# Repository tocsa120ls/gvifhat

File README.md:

gvifhat - a RasPi hat that uses the DVI output to create a GVIF stream that can be fed into an Opel Ampera/Chevy Volt's central display
---------------------------------------------------------------------------------------------------------------------------------------

### It also has an AR1100 HID to capture the touches from the display and feed it back to the RasPi. (and an RTC)

Proof-of-Concept video: [YouTube](https://youtube.com/shorts/U-wecjOfMDg?feature=share)

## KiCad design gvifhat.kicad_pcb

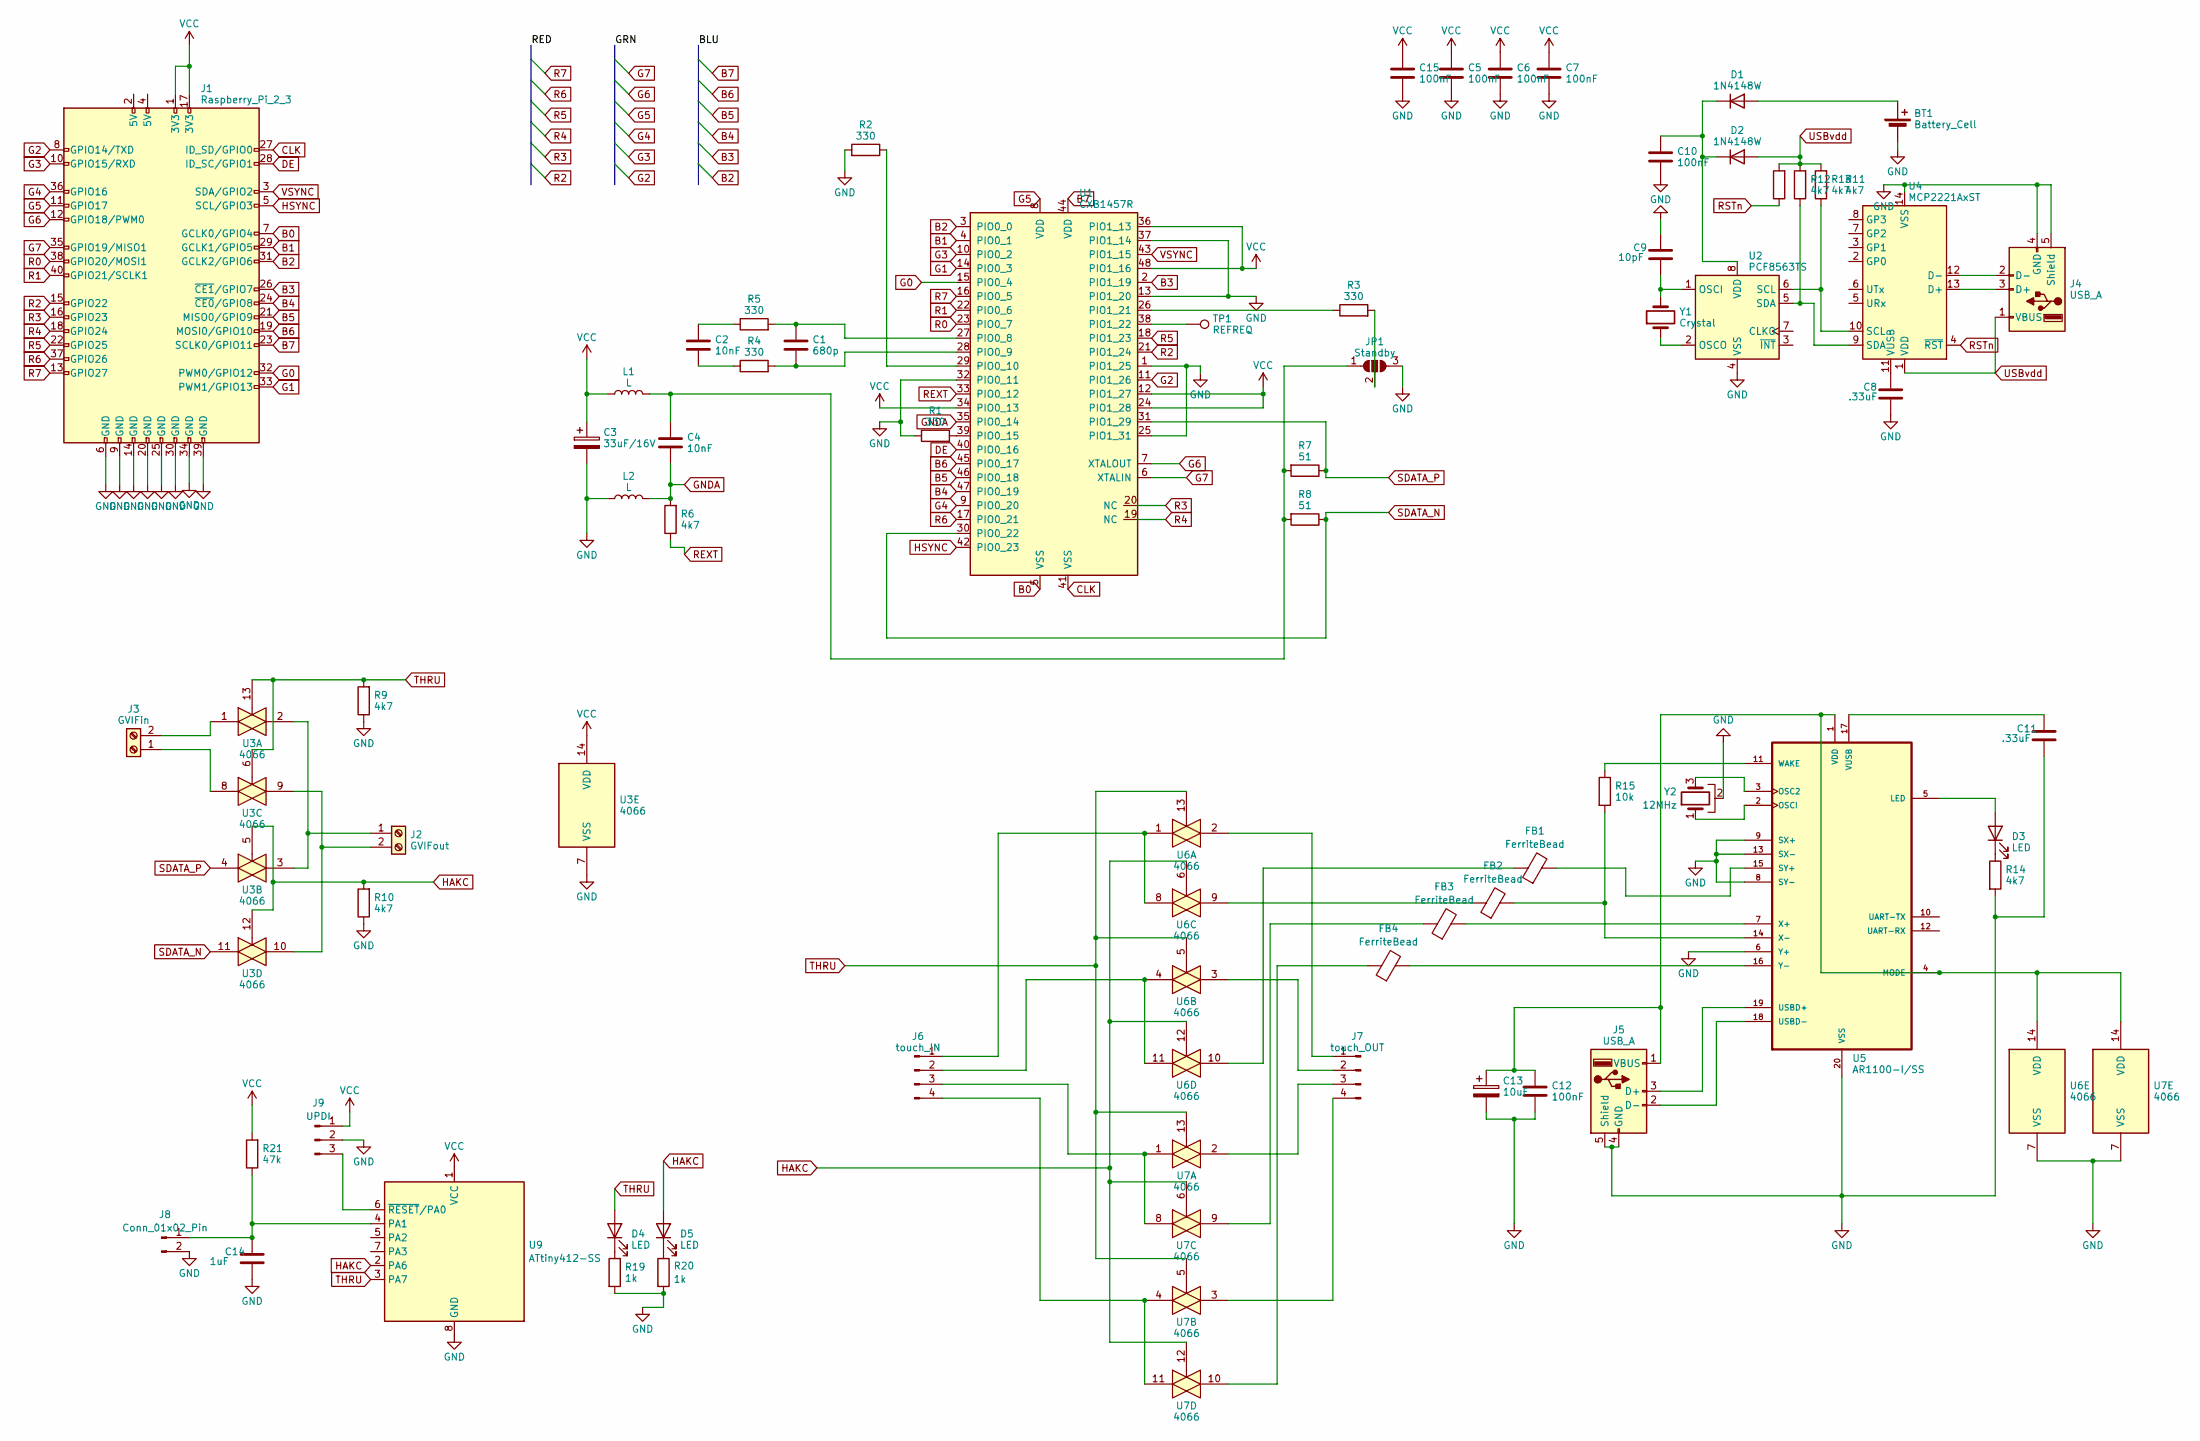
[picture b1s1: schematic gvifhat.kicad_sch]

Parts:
BT1: Battery_Cell; MPD_BC501SM-TR
C1: 680p; C_0603_1608Metric_Pad1.08x0.95mm_HandSolder
C2, C4: 10nF; C_0603_1608Metric_Pad1.08x0.95mm_HandSolder
C3: 33uF/16V; CP_EIA-6032-15_Kemet-U
C5, C6, C7, C10, C12, C15: 100nF; C_0603_1608Metric_Pad1.08x0.95mm_HandSolder
C8, C11: .33uF; C_0603_1608Metric_Pad1.08x0.95mm_HandSolder
C9: 10pF; C_0603_1608Metric_Pad1.08x0.95mm_HandSolder
C13: 10uF; CP_EIA-6032-15_Kemet-U
C14: 1uF; C_0603_1608Metric_Pad1.08x0.95mm_HandSolder
D1, D2: 1N4148W; D_SOD-123
D3, D4, D5: LED; LED_0603_1608Metric_Pad1.05x0.95mm_HandSolder
FB1, FB2, FB3, FB4: FerriteBead; R_0603_1608Metric
J1: Raspberry_Pi_2_3; MODULE_RASPBERRY_PI_4B_4GB
J2: GVIFout; TerminalBlock_Altech_AK300-2_P5.00mm
J3: GVIFin; TerminalBlock_Altech_AK300-2_P5.00mm
J4, J5: USB_A; USB_A_Molex_105057_Vertical
J6: touch_IN; FPC-SMD_3P-P1.00_AFA10-S03ECC-00
J7: touch_OUT; FPC-SMD_3P-P1.00_AFA10-S03ECC-00
J8: Conn_01x02_Pin; PinHeader_1x02_P2.54mm_Vertical
J9: UPDI; PinHeader_1x03_P2.54mm_Vertical
JP1: Standby; SolderJumper-3_P1.3mm_Bridged12_RoundedPad1.0x1.5mm
L1, L2: L; L_0603_1608Metric_Pad1.05x0.95mm_HandSolder
R1, R2, R3, R4, R5: 330; R_0603_1608Metric_Pad0.98x0.95mm_HandSolder
R6, R9, R10, R11, R12, R13, R14: 4k7; R_0603_1608Metric_Pad0.98x0.95mm_HandSolder
R7, R8: 51; R_0603_1608Metric_Pad0.98x0.95mm_HandSolder
R15: 10k; R_0603_1608Metric_Pad0.98x0.95mm_HandSolder
R19, R20: 1k; R_0603_1608Metric_Pad0.98x0.95mm_HandSolder
R21: 47k; R_0603_1608Metric_Pad0.98x0.95mm_HandSolder
TP1: REFREQ; TestPoint_Loop_D2.50mm_Drill1.0mm
U1: CXB1457R; LQFP-48_7x7mm_P0.5mm
U2: PCF8563TS; MSOP-8_3x3mm_P0.65mm
U3, U6, U7: 4066; SO-14_5.3x10.2mm_P1.27mm
U4: MCP2221AxST; SO-14_3.9x8.65mm_P1.27mm
U5: AR1100-I/SS; SOP65P780X200-20N
U9: ATtiny412-SS; SOIC-8_3.9x4.9mm_P1.27mm
Y1: Crystal; Crystal_SMD_3215-2Pin_3.2x1.5mm
Y2: 12MHz; Crystal_SMD_3225-4Pin_3.2x2.5mm

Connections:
B0: J1.7 (GCLK0/GPIO4), U1.5 (VSS)
B1: J1.29 (GCLK1/GPIO5), U1.4 (PIO0_1)
B2: J1.31 (GCLK2/GPIO6), U1.3 (PIO0_0)
B3: J1.26 (~CE1/GPIO7), U1.2 (PIO1_19)
B4: J1.24 (~CE0/GPIO8), U1.47 (PIO0_19)
B5: J1.21 (MISO0/GPIO9), U1.46 (PIO0_18)
B6: J1.19 (MOSI0/GPIO10), U1.45 (PIO0_17)
B7: J1.23 (SCLK0/GPIO11), U1.44 (VDD)
CLK: J1.27 (ID_SD/GPIO0), U1.41 (VSS)
DE: J1.28 (ID_SC/GPIO1), U1.40 (PIO0_16)
G0: J1.32 (PWM0/GPIO12), U1.15 (PIO0_4)
G1: J1.33 (PWM1/GPIO13), U1.14 (PIO0_3)
G2: J1.8 (GPIO14/TXD), U1.11 (PIO1_26)
G3: J1.10 (GPIO15/RXD), U1.10 (PIO0_2)
G4: J1.36 (GPIO16), U1.9 (PIO0_20)
G5: J1.11 (GPIO17), U1.8 (VDD)
G6: J1.12 (GPIO18/PWM0), U1.7 (XTALOUT)
G7: J1.35 (GPIO19/MISO1), U1.6 (XTALIN)
GND: BT1.2 (-), C3.2, C5.2, C6.2, C7.2, C8.2, C9.1, C10.2, C11.2, C12.2, C13.2, C14.2, C15.2, J1.6 (GND), J1.9 (GND), J1.14 (GND), J1.20 (GND), J1.25 (GND), J1.30 (GND), J1.39 (GND), J4.4 (GND), J4.5 (Shield), J5.4 (GND), J5.5 (Shield), J8.2, J9.2, JP1.3 (B), L2.1, R1.1, R2.2, R9.1, R10.1, R14.2, R19.2, R20.2, U1.1 (PIO1_25), U1.13 (PIO1_20), U1.25 (PIO1_31), U1.32 (PIO0_11), U1.37 (PIO1_14), U2.4 (VSS), U3.7 (VSS), U4.14 (VSS), U5.6 (Y+), U5.8 (SY-), U5.9 (SX+), U5.13 (SX-), U5.20 (VSS), U6.7 (VSS), U7.7 (VSS), U9.8 (GND), Y2.2; also elsewhere on the board
GNDA: C4.2, L2.2, R6.2, U1.35 (PIO0_14)
HAKC: D5.2 (A), R10.2, U3.5, U3.12, U6.6, U6.12, U7.6, U7.12, U9.2 (PA6)
HSYNC: J1.5 (SCL/GPIO3), U1.42 (PIO0_23)
unnamed: BT1.1 (+), D1.2 (A)
unnamed: C2.1, R5.1
unnamed: C2.2, R4.1
unnamed: C10.1, D1.1 (K), D2.1 (K), U2.8 (VDD)
unnamed: D3.2 (A), U5.5 (LED)
unnamed: D3.1 (K), R14.1
unnamed: D4.1 (K), R19.1
unnamed: D5.1 (K), R20.1
unnamed: FB1.1, U6.10
unnamed: FB2.1, U6.9
unnamed: FB3.1, U7.9
unnamed: FB4.1, U7.10
unnamed: J2.1, U3.2, U3.3
unnamed: J2.2, U3.9, U3.10
unnamed: J3.1, U3.8
unnamed: J3.2, U3.1
unnamed: J4.3 (D+), U4.13 (D+)
unnamed: J4.2 (D-), U4.12 (D-)
unnamed: J5.3 (D+), U5.19 (USBD+)
unnamed: J5.2 (D-), U5.18 (USBD-)
unnamed: C12.1, C13.1, J5.1 (VBUS), U5.1 (VDD), U5.4 (MODE), U6.14 (VDD), U7.14 (VDD)
unnamed: J6.1, U6.1, U6.8
unnamed: J6.2, U6.4, U6.11
unnamed: J6.3, U7.1, U7.8
unnamed: J6.4, U7.4, U7.11
unnamed: J7.1, U6.2
unnamed: J7.2, U6.3
unnamed: J7.3, U7.2
unnamed: J7.4, U7.3
unnamed 51: C14.1, J8.1, R21.1, U9.4 (PA1); also elsewhere on the board
unnamed 52: J9.3, U9.6 (~RESET/PA0); also elsewhere on the board
unnamed: C4.1, JP1.1 (A), L1.2, R7.2, R8.2
unnamed: JP1.2 (C), R3.2
unnamed: C1.1, R5.2, U1.27 (PIO0_8)
unnamed: C1.2, R4.2, U1.28 (PIO0_9)
unnamed: R2.1, U1.29 (PIO0_10)
unnamed: R1.2, U1.39 (PIO0_15)
unnamed: R3.1, U1.26 (PIO1_21)
unnamed: TP1.1, U1.38 (PIO1_22)
unnamed: C9.2, U2.1 (OSCI), Y1.2
unnamed: U2.2 (OSCO), Y1.1
unnamed: R13.1, U2.6 (SCL), U4.10 (SCL)
unnamed: R12.1, U2.5 (SDA), U4.9 (SDA)
unnamed: C8.1, U4.11 (VUSB)
unnamed: U5.3 (OSC2), Y2.3
unnamed: U5.2 (OSCI), Y2.1
unnamed: FB1.2, U5.15 (SY+)
unnamed: C11.1, U5.17 (VUSB)
unnamed: R15.1, U5.11 (WAKE)
unnamed: FB3.2, U5.7 (X+)
unnamed: FB2.2, R15.2, U5.14 (X-)
unnamed: FB4.2, U5.16 (Y-)
R0: J1.38 (GPIO20/MOSI1), U1.23 (PIO0_7)
R1: J1.40 (GPIO21/SCLK1), U1.22 (PIO0_6)
R2: J1.15 (GPIO22), U1.21 (PIO1_24)
R3: J1.16 (GPIO23), U1.20 (NC)
R4: J1.18 (GPIO24), U1.19 (NC)
R5: J1.22 (GPIO25), U1.18 (PIO1_23)
R6: J1.37 (GPIO26), U1.17 (PIO0_21)
R7: J1.13 (GPIO27), U1.16 (PIO0_5)
REXT: R6.1, U1.33 (PIO0_12)
RSTn: R11.1, U4.4 (~RST)
SDATA_N: R8.1, U1.30 (PIO0_22), U3.11
SDATA_P: R7.1, U1.31 (PIO1_29), U3.4
THRU: D4.2 (A), R9.2, U3.6, U3.13, U6.5, U6.13, U7.5, U7.13, U9.3 (PA7)
USBvdd: D2.2 (A), J4.1 (VBUS), R11.2, R12.2, R13.2, U4.1 (VDD)
VCC: C3.1, C5.1, C6.1, C7.1, C15.1, J1.1 (3V3), J1.17 (3V3), J9.1, L1.1, R21.2, U1.12 (PIO1_27), U1.24 (PIO1_28), U1.34 (PIO0_13), U1.36 (PIO1_13), U1.48 (PIO1_16), U3.14 (VDD), U9.1 (VCC); also elsewhere on the board
VSYNC: J1.3 (SDA/GPIO2), U1.43 (PIO1_15)

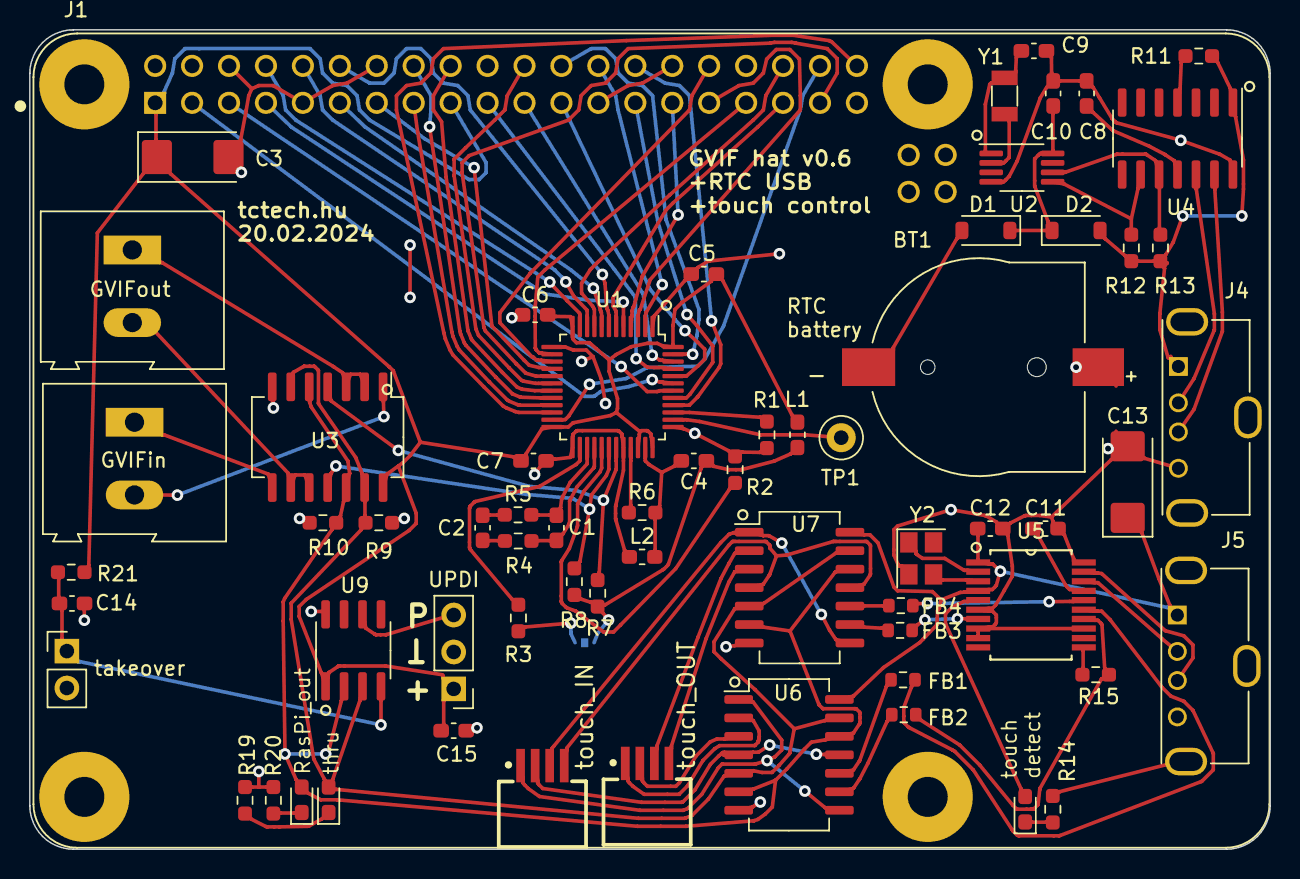
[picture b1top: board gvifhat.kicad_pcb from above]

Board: 2 copper layers, 85.3 x 56.4 mm, 66 parts (1 on the bottom side), 90 nets.

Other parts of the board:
UPDI: UPDI; PinHeader_1x03_P2.54mm_Vertical
takeover: Conn_01x02_Pin; PinHeader_1x02_P2.54mm_Vertical

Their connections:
GND: UPDI.2, takeover.2; also elsewhere on the board
unnamed 51: takeover.1; also elsewhere on the board
unnamed 52: UPDI.3; also elsewhere on the board
VCC: UPDI.1; also elsewhere on the board

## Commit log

2024-03-11 added ATtiny412 arduino sketch
2024-03-16 small PCB layout update
2024-03-18 replaced solder-in battery with a cr1220 holder
2024-03-18 new README
